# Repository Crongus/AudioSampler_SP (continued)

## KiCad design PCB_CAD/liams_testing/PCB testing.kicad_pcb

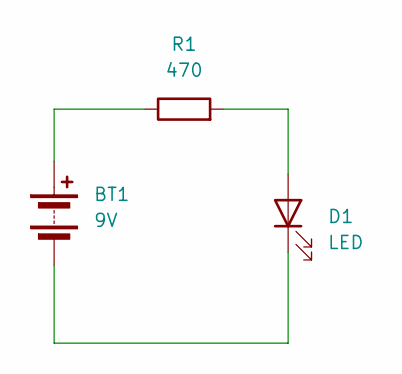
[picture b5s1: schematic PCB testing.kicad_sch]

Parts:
BT1: 9V; PinHeader_2x01_P2.54mm_Horizontal
D1: LED; LED_D5.0mm
R1: 470; R_Axial_DIN0309_L9.0mm_D3.2mm_P12.70mm_Horizontal

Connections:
unnamed: BT1.1 (+), R1.1
unnamed: BT1.2 (-), D1.1 (K)
unnamed: D1.2 (A), R1.2

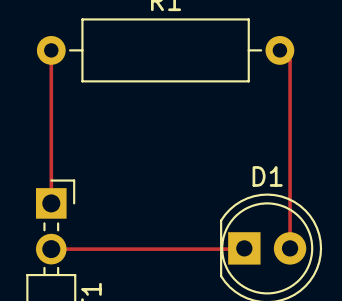
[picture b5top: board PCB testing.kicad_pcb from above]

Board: 2 copper layers, 3 parts (0 on the bottom side), 3 nets.

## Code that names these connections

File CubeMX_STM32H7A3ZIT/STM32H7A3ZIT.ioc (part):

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Mcu.Name=STM32H7A3Z(G-I)Tx
Mcu.Package=LQFP144
Mcu.UserName=STM32H7A3ZITx
PA11.GPIOParameters=GPIO_PuPd
PA11.GPIO_PuPd=GPIO_NOPULL
PA11.Mode=Device_Only_FS
PA11.Signal=USB_OTG_HS_DM
PA12.GPIOParameters=GPIO_PuPd
PA12.GPIO_PuPd=GPIO_PULLUP
PA12.Mode=Device_Only_FS
PA12.Signal=USB_OTG_HS_DP
PA13.Mode=Serial_Wire
PA13.Signal=DEBUG_JTMS-SWDIO
PA14.Mode=Serial_Wire
PA14.Signal=DEBUG_JTCK-SWCLK
PA15.Mode=Half_Duplex_Master_Rx
PA15.Signal=I2S1_WS
PA5.Mode=Half_Duplex_Master_Rx
PA5.Signal=I2S1_CK
PA6.Mode=Half_Duplex_Master_Rx
PA6.Signal=I2S1_SDI
PA9.Mode=Activate_VBUS_FS
PA9.Signal=USB_OTG_HS_VBUS
PB10.Mode=I2C
PB10.Signal=I2C2_SCL
PB11.Mode=I2C
PB11.Signal=I2C2_SDA
PB12.Mode=Half_Duplex_Master_Tx
PB12.Signal=I2S2_WS
PB13.Mode=Half_Duplex_Master_Tx
PB13.Signal=I2S2_CK
PB6.Mode=I2C
PB6.Signal=I2C1_SCL
PB7.Mode=I2C
PB7.Signal=I2C1_SDA
PC0.Signal=FMC_SDNWE
PC1.Mode=Half_Duplex_Master_Tx
PC1.Signal=I2S2_SDO
PC13.GPIOParameters=GPIO_PuPd,GPIO_Label,GPIO_ModeDefaultOutputPP
PC13.GPIO_Label=Keypad R3
PC13.GPIO_ModeDefaultOutputPP=GPIO_MODE_OUTPUT_PP
PC13.GPIO_PuPd=GPIO_NOPULL
PC13.Signal=GPIO_Output
PC14-OSC32_IN.GPIOParameters=GPIO_PuPd,GPIO_Label,GPIO_ModeDefaultEXTI
PC14-OSC32_IN.GPIO_Label=Keypad C2
PC14-OSC32_IN.GPIO_ModeDefaultEXTI=GPIO_MODE_IT_FALLING
PC14-OSC32_IN.GPIO_PuPd=GPIO_PULLUP
PC14-OSC32_IN.Signal=GPXTI14
PC15-OSC32_OUT.GPIOParameters=GPIO_PuPd,GPIO_Label,GPIO_ModeDefaultEXTI
PC15-OSC32_OUT.GPIO_Label=Keypad C1
PC15-OSC32_OUT.GPIO_ModeDefaultEXTI=GPIO_MODE_IT_FALLING
PC15-OSC32_OUT.GPIO_PuPd=GPIO_PULLUP
PC15-OSC32_OUT.Signal=GPXTI15
PC2_C.Mode=SdramChipSelect1_1
PC2_C.Signal=FMC_SDNE0
PC3_C.Mode=SdramChipSelect1_1
PC3_C.Signal=FMC_SDCKE0
PC4.Mode=Master_Clock_Activated
PC4.Signal=I2S1_MCK
PC6.Mode=Master_Clock_Activated
PC6.Signal=I2S2_MCK
PC8.Mode=NandChipSelect3_1
PC8.Signal=FMC_NCE
PD0.Signal=FMC_D2_DA2
PD1.Signal=FMC_D3_DA3
PD10.Signal=FMC_D15_DA15
PD11.Signal=FMC_A16_CLE
PD12.Signal=FMC_A17_ALE
PD14.Signal=FMC_D0_DA0
PD15.Signal=FMC_D1_DA1
PD4.Signal=FMC_NOE
PD5.Signal=FMC_NWE
PD6.Signal=FMC_NWAIT
PD7.Mode=IN0
PD7.Signal=SPDIFRX_IN0
PD8.Signal=FMC_D13_DA13
PD9.Signal=FMC_D14_DA14
PE0.Signal=FMC_NBL0
PE1.Signal=FMC_NBL1
PE10.Signal=FMC_D7_DA7
PE11.Signal=FMC_D8_DA8
PE12.Signal=FMC_D9_DA9
PE13.Signal=FMC_D10_DA10
PE14.Signal=FMC_D11_DA11
PE15.Signal=FMC_D12_DA12
PE2.GPIOParameters=GPIO_PuPd,GPIO_Label,GPIO_ModeDefaultEXTI
PE2.GPIO_Label=Keypad C5
PE2.GPIO_ModeDefaultEXTI=GPIO_MODE_IT_FALLING
PE2.GPIO_PuPd=GPIO_PULLUP
PE2.Signal=GPXTI2
PE3.GPIOParameters=GPIO_PuPd,GPIO_Label,GPIO_ModeDefaultEXTI
PE3.GPIO_Label=Keypad C4
PE3.GPIO_ModeDefaultEXTI=GPIO_MODE_IT_FALLING
PE3.GPIO_PuPd=GPIO_PULLUP
PE3.Signal=GPXTI3
PE4.GPIOParameters=GPIO_Speed,GPIO_PuPd,GPIO_Label,GPIO_ModeDefaultOutputPP
PE4.GPIO_Label=Keypad R1
PE4.GPIO_ModeDefaultOutputPP=GPIO_MODE_OUTPUT_PP
PE4.GPIO_PuPd=GPIO_NOPULL
PE4.GPIO_Speed=GPIO_SPEED_FREQ_VERY_HIGH
PE4.Signal=GPIO_Output
PE5.GPIOParameters=GPIO_PuPd,GPIO_Label,GPIO_ModeDefaultEXTI
PE5.GPIO_Label=Keypad C3
PE5.GPIO_ModeDefaultEXTI=GPIO_MODE_IT_FALLING
PE5.GPIO_PuPd=GPIO_PULLUP
PE5.Signal=GPXTI5
PE6.GPIOParameters=GPIO_Speed,GPIO_PuPd,GPIO_Label,GPIO_ModeDefaultOutputPP
PE6.GPIO_Label=Keypad R2
PE6.GPIO_ModeDefaultOutputPP=GPIO_MODE_OUTPUT_PP
PE6.GPIO_PuPd=GPIO_NOPULL
PE6.GPIO_Speed=GPIO_SPEED_FREQ_VERY_HIGH
PE6.Signal=GPIO_Output
PE7.Signal=FMC_D4_DA4
PE8.Signal=FMC_D5_DA5
PE9.Signal=FMC_D6_DA6
PF0.Signal=FMC_A0
PF1.Signal=FMC_A1
PF11.Signal=FMC_SDNRAS
PF12.Signal=FMC_A6
PF13.Signal=FMC_A7
PF14.Signal=FMC_A8
PF15.Signal=FMC_A9
PF2.Signal=FMC_A2
PF3.Signal=FMC_A3
PF4.Signal=FMC_A4
PF5.Signal=FMC_A5
PF6.Signal=GPIO_Output
PF7.GPIOParameters=GPIO_Speed,GPIO_PuPd,GPIO_Label,GPIO_ModeDefaultOutputPP
PF7.GPIO_Label=Keypad R4
PF7.GPIO_ModeDefaultOutputPP=GPIO_MODE_OUTPUT_PP
PF7.GPIO_PuPd=GPIO_NOPULL
PF7.GPIO_Speed=GPIO_SPEED_FREQ_VERY_HIGH
PF7.Signal=GPIO_Output
PG0.Signal=FMC_A10
PG1.Signal=FMC_A11
PG15.Signal=FMC_SDNCAS
PG4.Signal=FMC_A14_BA0
PG5.Signal=FMC_A15_BA1
PG8.Signal=FMC_SDCLK
RCC.SYSCLKFreq_VALUE=280000000
RCC.SYSCLKSource=RCC_SYSCLKSOURCE_PLLCLK
board=custom

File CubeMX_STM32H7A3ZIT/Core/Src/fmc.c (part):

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  __HAL_RCC_FMC_CLK_ENABLE();

  /** FMC GPIO Configuration
  PF0   ------> FMC_A0
  PF1   ------> FMC_A1
  PF2   ------> FMC_A2
  PF3   ------> FMC_A3
  PF4   ------> FMC_A4
  PF5   ------> FMC_A5
  PC0   ------> FMC_SDNWE
  PC2_C   ------> FMC_SDNE0
  PC3_C   ------> FMC_SDCKE0
  PF11   ------> FMC_SDNRAS
  PF12   ------> FMC_A6
  PF13   ------> FMC_A7
  PF14   ------> FMC_A8
  PF15   ------> FMC_A9
  PG0   ------> FMC_A10
  PG1   ------> FMC_A11
  PE7   ------> FMC_D4
  PE8   ------> FMC_D5
  PE9   ------> FMC_D6
  PE10   ------> FMC_D7
  PE11   ------> FMC_D8
  PE12   ------> FMC_D9
  PE13   ------> FMC_D10
  PE14   ------> FMC_D11
  PE15   ------> FMC_D12
  PD8   ------> FMC_D13
  PD9   ------> FMC_D14
  PD10   ------> FMC_D15
  PD11   ------> FMC_CLE
  PD12   ------> FMC_ALE
  PD14   ------> FMC_D0
  PD15   ------> FMC_D1
  PG4   ------> FMC_BA0
  PG5   ------> FMC_BA1
  PG8   ------> FMC_SDCLK
  PC8   ------> FMC_NCE
  PD0   ------> FMC_D2
  PD1   ------> FMC_D3
  PD4   ------> FMC_NOE
  PD5   ------> FMC_NWE
  PD6   ------> FMC_NWAIT
  PG15   ------> FMC_SDNCAS
  PE0   ------> FMC_NBL0
  PE1   ------> FMC_NBL1
  */
  /* GPIO_InitStruct */
  GPIO_InitStruct.Pin = GPIO_PIN_0|GPIO_PIN_1|GPIO_PIN_2|GPIO_PIN_3
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  __HAL_RCC_FMC_CLK_DISABLE();

  /** FMC GPIO Configuration
  PF0   ------> FMC_A0
  PF1   ------> FMC_A1
  PF2   ------> FMC_A2
  PF3   ------> FMC_A3
  PF4   ------> FMC_A4
  PF5   ------> FMC_A5
  PC0   ------> FMC_SDNWE
  PC2_C   ------> FMC_SDNE0
  PC3_C   ------> FMC_SDCKE0
  PF11   ------> FMC_SDNRAS
  PF12   ------> FMC_A6
  PF13   ------> FMC_A7
  PF14   ------> FMC_A8
  PF15   ------> FMC_A9
  PG0   ------> FMC_A10
  PG1   ------> FMC_A11
  PE7   ------> FMC_D4
  PE8   ------> FMC_D5
  PE9   ------> FMC_D6
  PE10   ------> FMC_D7
  PE11   ------> FMC_D8
  PE12   ------> FMC_D9
  PE13   ------> FMC_D10
  PE14   ------> FMC_D11
  PE15   ------> FMC_D12
  PD8   ------> FMC_D13
  PD9   ------> FMC_D14
  PD10   ------> FMC_D15
  PD11   ------> FMC_CLE
  PD12   ------> FMC_ALE
  PD14   ------> FMC_D0
  PD15   ------> FMC_D1
  PG4   ------> FMC_BA0
  PG5   ------> FMC_BA1
  PG8   ------> FMC_SDCLK
  PC8   ------> FMC_NCE
  PD0   ------> FMC_D2
  PD1   ------> FMC_D3
  PD4   ------> FMC_NOE
  PD5   ------> FMC_NWE
  PD6   ------> FMC_NWAIT
  PG15   ------> FMC_SDNCAS
  PE0   ------> FMC_NBL0
  PE1   ------> FMC_NBL1
  */

  HAL_GPIO_DeInit(GPIOF, GPIO_PIN_0|GPIO_PIN_1|GPIO_PIN_2|GPIO_PIN_3
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
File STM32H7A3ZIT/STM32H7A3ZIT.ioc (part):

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Mcu.Name=STM32H7A3Z(G-I)Tx
Mcu.Package=LQFP144
Mcu.UserName=STM32H7A3ZITx
PA15.Mode=Full_Duplex_Master
PA15.Signal=I2S1_WS
PA4.Mode=Full_Duplex_Master
PA4.Signal=I2S3_WS
PA5.Mode=Full_Duplex_Master
PA5.Signal=I2S1_CK
PA6.Mode=Full_Duplex_Master
PA6.Signal=I2S1_SDI
PA7.Mode=Full_Duplex_Master
PA7.Signal=I2S1_SDO
PB10.Mode=Full_Duplex_Master
PB10.Signal=I2S2_CK
PB12.Mode=Full_Duplex_Master
PB12.Signal=I2S2_WS
PB14.Mode=Full_Duplex_Master
PB14.Signal=I2S2_SDI
PB2.Mode=Full_Duplex_Master
PB2.Signal=I2S3_SDO
PC10.Mode=Full_Duplex_Master
PC10.Signal=I2S3_CK
PC11.Mode=Full_Duplex_Master
PC11.Signal=I2S3_SDI
PC3_C.Mode=Full_Duplex_Master
PC3_C.Signal=I2S2_SDO
PC8.Mode=NandChipSelect3_1
PC8.Signal=FMC_NCE
PD0.Signal=FMC_D2_DA2
PD1.Signal=FMC_D3_DA3
PD10.Signal=FMC_D15_DA15
PD11.Signal=FMC_A16_CLE
PD12.Signal=FMC_A17_ALE
PD14.Signal=FMC_D0_DA0
PD15.Signal=FMC_D1_DA1
PD4.Signal=FMC_NOE
PD5.Signal=FMC_NWE
PD7.Mode=IN0
PD7.Signal=SPDIFRX_IN0
PD8.Signal=FMC_D13_DA13
PD9.Signal=FMC_D14_DA14
PE10.Signal=FMC_D7_DA7
PE11.Signal=FMC_D8_DA8
PE12.Signal=FMC_D9_DA9
PE13.Signal=FMC_D10_DA10
PE14.Signal=FMC_D11_DA11
PE15.Signal=FMC_D12_DA12
PE7.Signal=FMC_D4_DA4
PE8.Signal=FMC_D5_DA5
PE9.Signal=FMC_D6_DA6
RCC.SYSCLKFreq_VALUE=64000000
board=custom

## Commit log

2024-09-13 testing commit functionality
2024-09-23 WIP parts list w/reasoning, kicad sample project for practice
2024-09-23 Added 'Important Photos', 'liams_practice' and 'STM32MX_DevBoard', which are all things I was working on without committing
2024-09-26 add useful crash course on DRAM operation cribbed from SBU
2024-09-26 observations and questions on RAM and PSU selection in PARTS.txt
2024-09-27 Adding New stm32cubemx project for the actual board we plan on using
2024-09-27 new list of parts and rationales with latest developments in memory ideas
2024-09-30 updated the CubeMX project for the controller: configured some of the flash memory
2024-09-30 parts list: ADC, DAC, SPDIF tx, Toslink tx&rx, microcontroller
2024-10-01 Parts list substantively complete including PSU, ready for an order pending final review.
2024-10-01 added the schematic for the external flash to KICad and added the it and the microcontroller to the schematic design
2024-10-02 Connected all data and logic lines from flash to ucontroller. Power lines still unconnected
2024-10-02 added organization to the datasheets in the repo
2024-10-02 added ADC datasheet to datasheet folder
2024-10-02 all datasheets for present revision of PARTS
2024-10-02 add DIX9211 CAD model
2024-10-02 added adc pinout kicad project so Isaac and I can work on kicad simultaneously. made pin connections in aforementioned project
2024-10-04 Changed some i2s configuation in stm32cubeMX, continued to update pinouts for the ADC
2024-10-04 CAD models and symbols
2024-10-04 added my adc pinouts to main circuit schematic in kicad
2024-10-04 remove the extremely obnoxious big red box from the schematic file in kicad
2024-10-04 RAM CAD models
2024-10-07 finalized PSU decision, added solderable receptacle
2024-10-09 made some small changes to kicad schematic to print
2024-10-10 schematic add NAU8402WG DAC
2024-10-11 add spdif tx output, fixed DIX9211 cad model
2024-10-23 idk its been a while
2024-10-24 assorted additions and small changes for past week
2024-10-24 PSU CAD models
2024-10-24 logic level shifter
2024-10-24 added pcb order 2 forlder and completed the adc and flash on the new schematic
2024-10-27 completed kicad schematic barring only the PSU, supply line filtering, digital RCA and logic level shifters
2024-10-27 LLS CAD models
2024-10-27 added RCA connections, and logic level shifters to kicad schematic
2024-10-27 added vdd_div voltage divider. Schematic now substantively complete barring noise filtering on power lines and PSU
2024-10-28 power supply decoupling work
2024-10-29 menial changes to kicad
2024-10-29 digital in, digital out, analog out complete
2024-10-31 readded switch symbol that was lost in commit hell
2024-10-31 latched footprints to each symbol in the kicad schematic
2024-10-31 added 4 layers to the pcb
2024-10-31 moved some stuff on pcb
2024-11-01 continued progress on pcb design
2024-11-04 more pcb design things. RAM and Flash wiring
2024-11-04 power daughterboard complete schematic, some more CAD models
2024-11-05 added high speed pcb design pdf
2024-11-05 finally found out about manhattan routing. Significant progress made
2024-11-06 pcb layout stuff
2024-11-06 power daughterboard work
2024-11-06 added i2s2 pins on kicad schematic
2024-11-06 corrected 1 small i2s2 error
2024-11-06 pcb'd dix9211 and lss with power
2024-11-07 current schematic work from Isaac's side
2024-11-07 grayhill keypad datasheet
2024-11-07 dac power and digital out done
2024-11-12 updating things
2024-11-12 schematic fix adc, voltage divider, keypad, update cubeMX with kp pins
2024-11-13 added footprints
2024-11-13 pinned out adc power filtering and header for the keypad
2024-11-14 cubeMX and schematic add LCD, some work on RAM and ucontroller power
2024-11-14 added footprints to schematic
2024-11-14 fix conflict
2024-11-15 work on power daughterboard
2024-11-15 schematic fixes and add USB, cubeMX update, add more useful documents
2024-11-16 changed config settings in cubemx
2024-11-16 declared clip variables
2024-11-16 schematic substantively complete (for real) (version 3.0) (final) (last)
2024-11-16 added pcb_order3
2024-11-16 minor fix microcontroller FMC
2024-11-17 made it so cubemx doesnt change pins around and deleted i2s3
2024-11-17 change i2s configuration
2024-11-17 started pcb design
2024-11-17 schematic power entry, schematic and cubeMX SW debug
2024-11-18 pinned out 3 sides of the microcontroller
2024-11-19 power daughterboard finished
2024-11-19 power daughterboard final review, some main schematic small fixes
2024-11-19 finished pinning out the microcontroller
2024-11-19 second attempt to add dix9211 power
2024-11-19 complete? pcb design
2024-11-19 final schematic review minus debug ports (USB and SW)
2024-11-19 cleaned up silkscreen and added ground planes
2024-11-20 rectify current working copies
2024-11-20 change digital out blocks to use toslink
2024-11-20 pcb emergency tosling complete. working on power
2024-11-20 power 'T's complete
2024-11-21 preserve current PCB state, substantively ready to go to fab but messy on small details
2024-11-21 Main board final review complete and Gerbers generated. This board would cost 40 bucks extra at JLC because of the 20/35 vias, preferentially needs updated to minimally 30/45 vias if we do not want t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
2024-11-21 fixed via size and clearance issues
2024-11-21 Our long national nightmare is over
2024-11-22 Gold master PCB designs as submitted to JLC
2024-11-22 pregenerated cubemx code compiles
2024-11-23 cubeide stuff
2024-11-23 ECE271 Code added
2024-11-23 bad attempt at setting up dev board for keypad and LCD work
2024-12-01 adding from isaacs old laptop
2024-12-02 annoying merge conflict
2024-12-02 attempted to get ram working
2024-12-02 good progress on setting up keypad and lcd with dev board
2024-12-03 skeleton of keypad algorithm assembled
2024-12-04 Com Port working, ram not
2024-12-05 modularized keypad code, started on LCD code. TBD validate functionality of newly modularized keypad functions, there might be some loonie tunes corner case
2024-12-06 cant get ram working
2024-12-06 keypad and LCD code fully modularized and fully gold
2024-12-07 assorted work from yesterday I forgot to commit
2024-12-07 Hardfault in external ram solved
2024-12-09 test code for ram
2024-12-09 ram completely completed, all addresses data good
2024-12-10 flash not working :(
2024-12-12 flash hardfault fixed, begin work on interrupts
2024-12-12 update for avoiding conflict hell 12/12
2024-12-12 port lcd and keypad code to real thing
2024-12-13 prove keypad works with the real thing
2024-12-17 unstupidified the flash code. Still doesnt work. about to start turning the keypad to interrupts
2024-12-18 barely working analog in and out
2024-12-18 trying to get i2s dma working
2024-12-18 dumb local files merge conflict hell
2024-12-19 final commit before design review so we can print our source code
2025-01-31 test from new laptop
2025-02-05 moved USB module, good progress on hooking up ADC to USB5V
2025-02-07 more work on USB and Toslink
2025-02-10 board work, SWD and boot switches, user IO block
2025-02-14 board work, shrink board, audio IO block, I2C, TVS
2025-02-19 board work mostly minor cleanup. starting DIX9211 rerouting soon
2025-02-24 menial changes, commit before trying to shrink data size
2025-02-24 board work, move debug block in preparation for rewiring DIX9211. GPIO pin for SPDIF error interrupt will be 111, but didn't update CubeMX
2025-03-03 4x size reduction and expantion
2025-03-03 Data expantion not functional
2025-03-03 substantive board revisions complete, needs one good review pass. CubeMX updated for I2S3 and DIR interrupt line
2025-03-07 Working on DMA transfers. its not working rn
2025-03-10 working with DMA! No Clips, but works just as a passthrough
2025-04-02 Audio completely clear with RAM storage
2025-04-07 bad attempt at compression
2025-04-07 8khz 1 channel signal. about to start making clips
2025-04-08 Clear fully working 12 clips
2025-04-08 Working pitch control
2025-04-09 Maybe high quality mode working (untested)
2025-04-25 Adding csv files
2025-04-28 adding the freq response csv
